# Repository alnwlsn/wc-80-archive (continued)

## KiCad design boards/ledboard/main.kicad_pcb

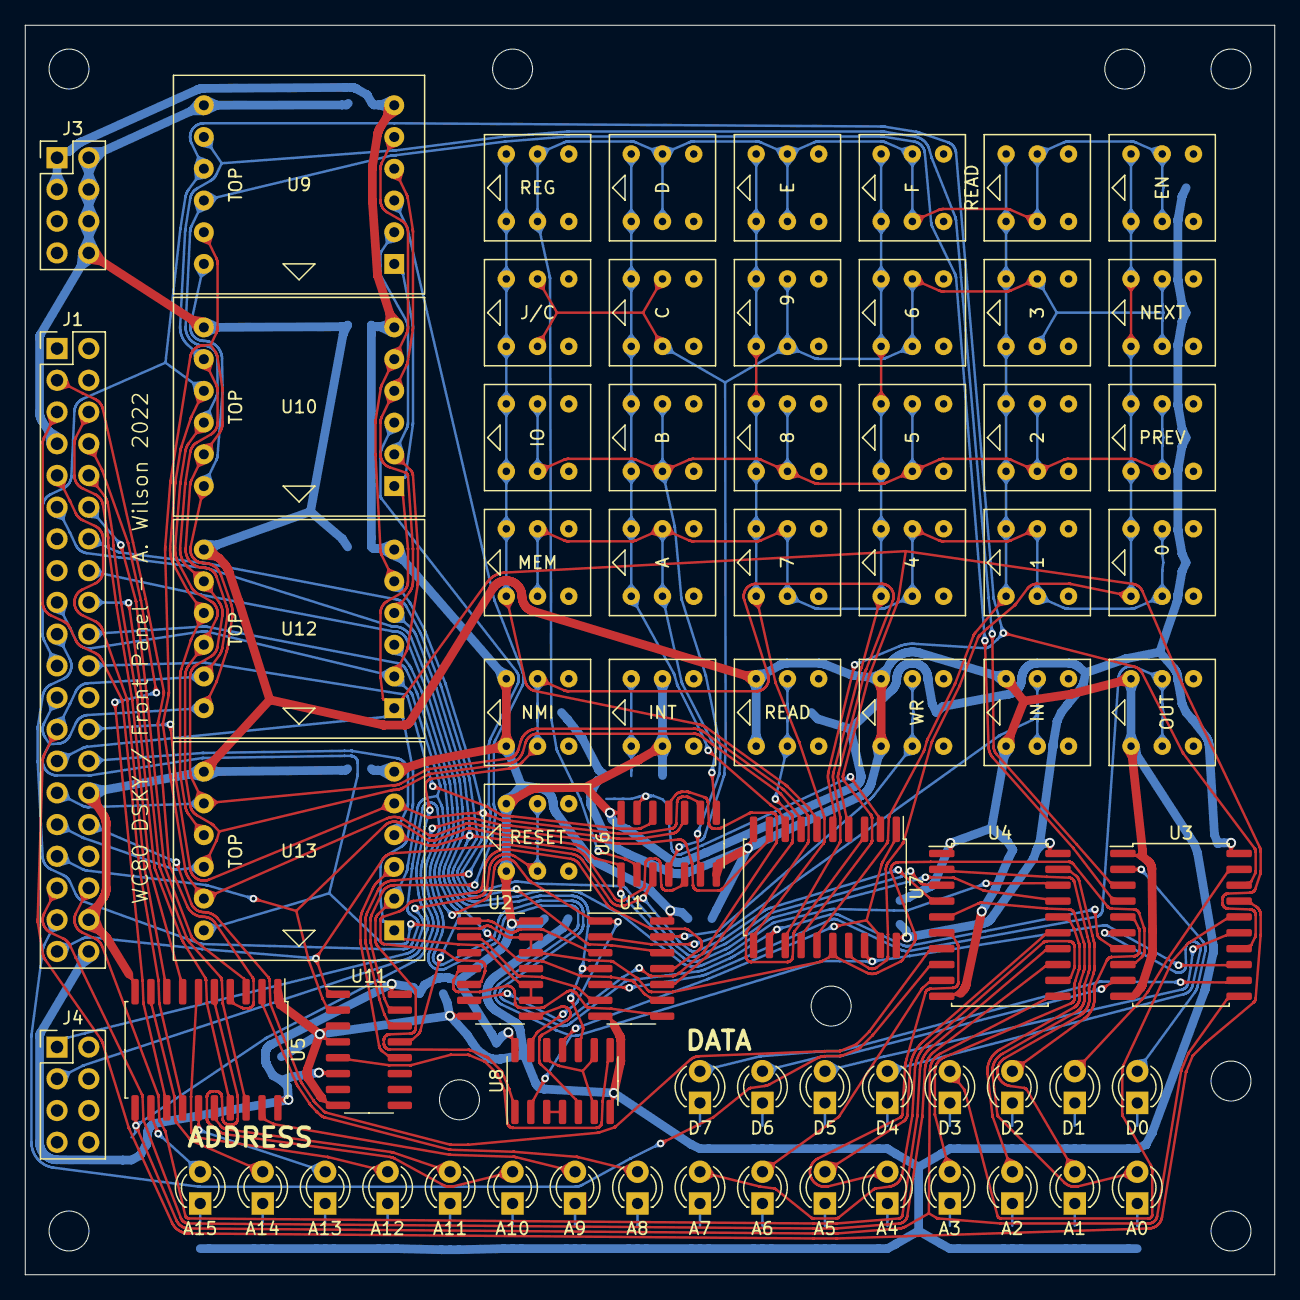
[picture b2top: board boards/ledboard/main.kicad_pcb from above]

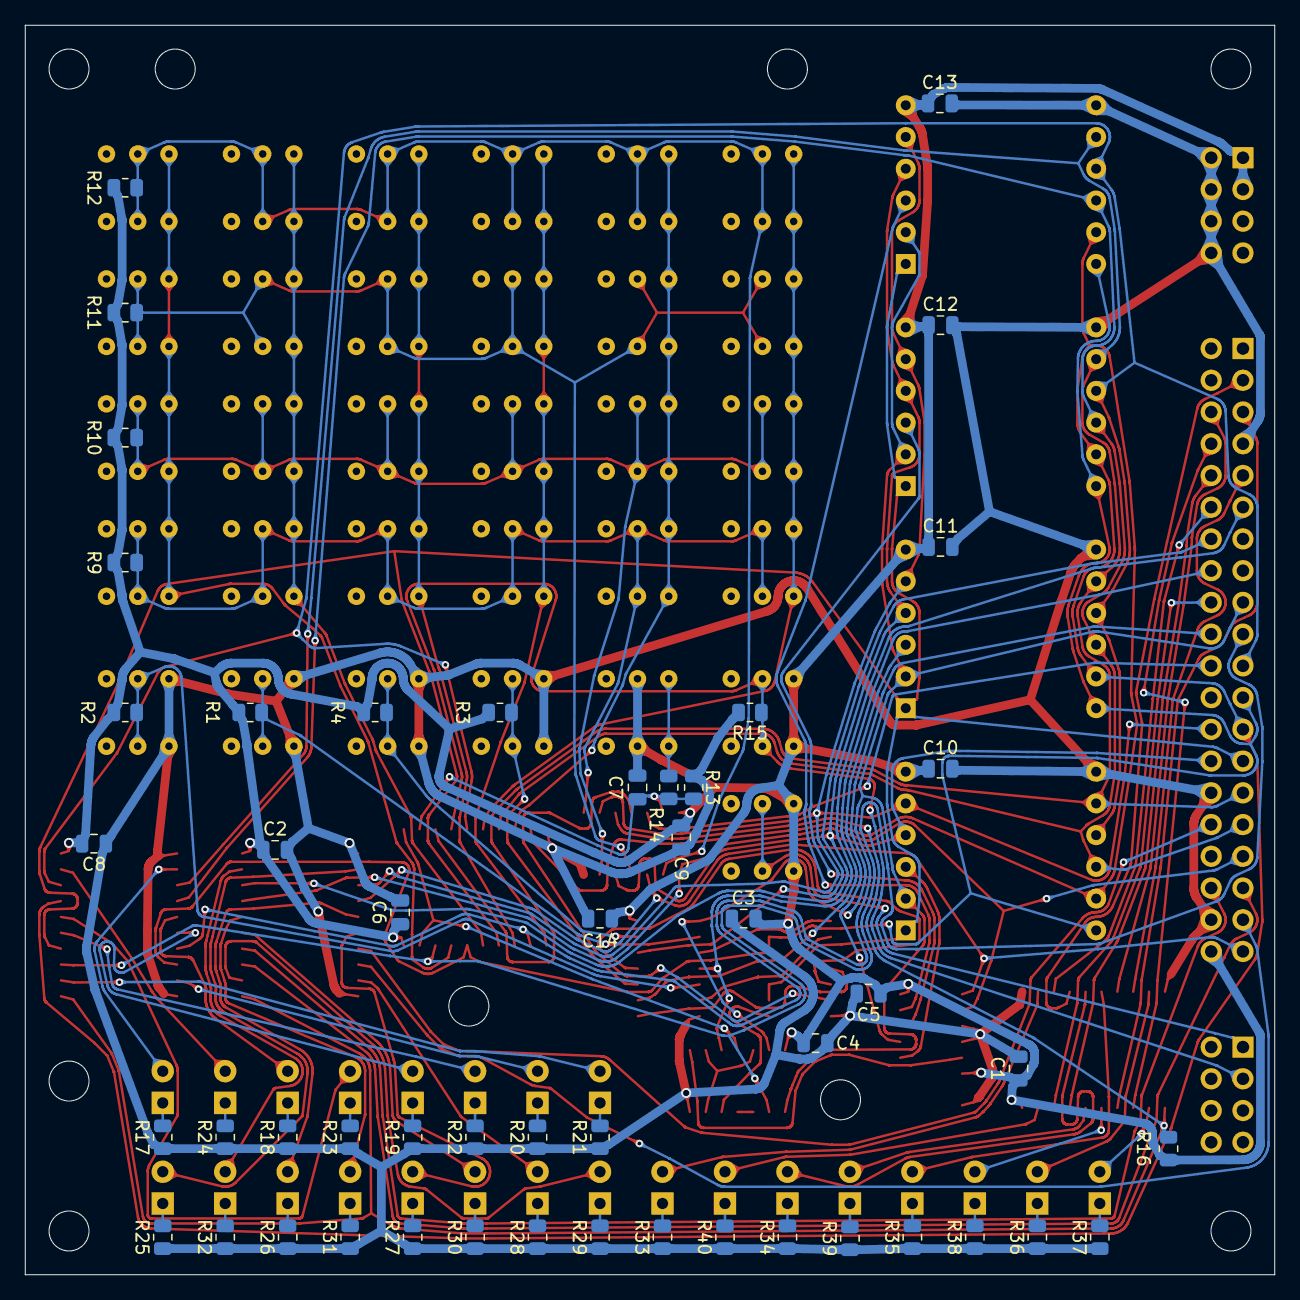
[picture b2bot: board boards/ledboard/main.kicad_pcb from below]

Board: 2 copper layers, 100.0 x 100.0 mm, 130 parts (50 on the bottom side), 112 nets.

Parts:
C1, C2, C3, C4, C5, C6, C7, C8, C9, C10, C11, C12, C13, C14: 100n; C_0805_2012Metric
D1: D0; LED_D3.0mm_FlatTop
D2: D2; LED_D3.0mm_FlatTop
D3: D4; LED_D3.0mm_FlatTop
D4: D6; LED_D3.0mm_FlatTop
D5: D7; LED_D3.0mm_FlatTop
D6: D5; LED_D3.0mm_FlatTop
D7: D3; LED_D3.0mm_FlatTop
D8: D1; LED_D3.0mm_FlatTop
D9: A0; LED_D3.0mm_FlatTop
D10: A2; LED_D3.0mm_FlatTop
D11: A4; LED_D3.0mm_FlatTop
D12: A6; LED_D3.0mm_FlatTop
D13: A7; LED_D3.0mm_FlatTop
D14: A5; LED_D3.0mm_FlatTop
D15: A3; LED_D3.0mm_FlatTop
D16: A1; LED_D3.0mm_FlatTop
D17: A8; LED_D3.0mm_FlatTop
D18: A10; LED_D3.0mm_FlatTop
D19: A12; LED_D3.0mm_FlatTop
D20: A14; LED_D3.0mm_FlatTop
D21: A15; LED_D3.0mm_FlatTop
D22: A13; LED_D3.0mm_FlatTop
D23: A11; LED_D3.0mm_FlatTop
D24: A9; LED_D3.0mm_FlatTop
H1, H2, H3, H4, H5, H6, H7, H8, H9: MountingHole; MountingHole_3.2mm_M3_DIN965
J1: TRS80W-header; PinHeader_2x20_P2.54mm_Vertical
J3, J4: Conn_02x04_Odd_Even; PinHeader_2x04_P2.54mm_Vertical
R1, R2, R3, R4, R9, R10, R11, R12, R13, R15, R16: 4.7K; R_0805_2012Metric
R14: 10; R_0805_2012Metric
R17, R18, R19, R20, R21, R22, R23, R24, R25, R26, R27, R28, R29, R30, R31, R32, R33, R34, R35, R36, R37, R38, R39, R40: 470; R_0805_2012Metric
SW1: IN; 8.5x8.5-DPDT-SP
SW2: OUT; 8.5x8.5-DPDT-SP
SW3, SW27: READ; 8.5x8.5-DPDT-SP
SW4: WR; 8.5x8.5-DPDT-SP
SW5: MEM; 8.5x8.5-DPDT-SP
SW6: A; 8.5x8.5-DPDT-SP
SW7: 7; 8.5x8.5-DPDT-SP
SW8: 4; 8.5x8.5-DPDT-SP
SW9: 1; 8.5x8.5-DPDT-SP
SW10: 0; 8.5x8.5-DPDT-SP
SW11: IO; 8.5x8.5-DPDT-SP
SW12: B; 8.5x8.5-DPDT-SP
SW13: 8; 8.5x8.5-DPDT-SP
SW14: 5; 8.5x8.5-DPDT-SP
SW15: 2; 8.5x8.5-DPDT-SP
SW16: PREV; 8.5x8.5-DPDT-SP
SW17: J/C; 8.5x8.5-DPDT-SP
SW18: C; 8.5x8.5-DPDT-SP
SW19: 9; 8.5x8.5-DPDT-SP
SW20: 6; 8.5x8.5-DPDT-SP
SW21: 3; 8.5x8.5-DPDT-SP
SW22: NEXT; 8.5x8.5-DPDT-SP
SW23: REG; 8.5x8.5-DPDT-SP
SW24: D; 8.5x8.5-DPDT-SP
SW25: E; 8.5x8.5-DPDT-SP
SW26: F; 8.5x8.5-DPDT-SP
SW28: EN; 8.5x8.5-DPDT-SP
SW29: INT; 8.5x8.5-DPDT-SP
SW30: RESET; 8.5x8.5-DPDT-SP
SW31: NMI; 8.5x8.5-DPDT-SP
U1, U8: 74LS32; SOIC-14_3.9x8.7mm_P1.27mm
U2: 74LS20; SOIC-14_3.9x8.7mm_P1.27mm
U3, U4, U5: 74LS374; SOIC-20W_7.5x12.8mm_P1.27mm
U6: 74LS06; SOIC-14_3.9x8.7mm_P1.27mm
U7: 74HCT244; SOIC-20W_7.5x12.8mm_P1.27mm
U9, U10, U12, U13: HPDL1414; DIP-24_W15.24mm_Socket
U11: 74LS138; SOIC-16_3.9x9.9mm_P1.27mm

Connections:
6x_IN: U7.1, U7.19, U8.11
6x_OUT: U8.8, U11.5
+5V: C1.1, C2.1, C3.1, C4.1, C5.1, C6.1, C7.2, C8.1, C9.1, C10.1, C11.1, C12.1, C13.1, C14.1, J1.40, J3.1, J3.3, R1.1, R2.1, R3.1, R4.1, R9.2, R10.2, R11.2, R12.2, R16.2, SW29.2, SW30.1, SW31.1, U1.14, U2.14, U3.20, U4.20, U5.20, U6.14, U7.20, U8.14, U9.6, U10.6, U11.6, U11.16, U12.6, U13.6
F_A0: J1.26, U4.3, U6.9, U9.5, U10.5, U12.5, U13.5
F_A1: J1.28, U4.18, U6.5, U9.4, U10.4, U12.4, U13.4
F_A2: J1.39, U4.4, U6.3, U11.1
F_A3: J1.33, U4.17, U6.1, U11.2
F_A4: J1.32, U4.7
F_A5: J1.36, U4.14
F_A6: J1.37, U4.8
F_A7: J1.35, U4.13
F_A8: J1.12, U5.3
F_A9: J1.18, U5.18
F_A10: J1.3, U5.4
F_A11: J1.10, U5.17
F_A12: J1.6, U5.7
F_A13: J1.5, U5.14
F_A14: J1.9, U5.8
F_A15: J1.8, U5.13
F_D0: J1.29, U3.3, U7.3, U9.8, U10.8, U12.8, U13.8
F_D1: J1.21, U3.18, U7.5, U9.9, U10.9, U12.9, U13.9
F_D2: J1.31, U3.4, U7.7, U9.10, U10.10, U12.10, U13.10
F_D3: J1.25, U3.17, U7.9, U9.11, U10.11, U12.11, U13.11
F_D4: J1.17, U3.7, U7.12, U8.1, U9.2, U10.2, U12.2, U13.2
F_D5: J1.27, U2.9, U2.10, U3.14, U7.14, U9.1, U10.1, U12.1, U13.1
F_D6: J1.23, U2.12, U2.13, U3.8, U7.16, U9.12, U10.12, U12.12, U13.12
F_D7: J1.19, U3.13, U7.18, U8.2
GND: C1.2, C2.2, C3.2, C4.2, C5.2, C6.2, C8.2, C9.2, C10.2, C11.2, C12.2, C13.2, C14.2, J1.7, J1.30, J1.38, J3.2, J3.4, J3.6, J3.8, R13.1, R15.2, R17.1, R18.1, R19.1, R20.1, R21.1, R22.1, R23.1, R24.1, R25.1, R26.1, R27.1, R28.1, R29.1, R30.1, R31.1, R32.1, R33.1, R34.1, R35.1, R36.1, R37.1, R38.1, R39.1, R40.1, SW1.1, SW2.1, SW3.1, SW4.1, U1.7, U2.7, U3.1, U3.10, U4.1, U4.10, U5.1, U5.10, U6.7, U7.10, U8.7, U9.7, U10.7, U11.3, U11.4, U11.8, U12.7, U13.7
unnamed: C7.1, R13.2, R14.2, U6.13, U7.2
unnamed: D1.1, R17.2
unnamed: D1.2, U3.2
unnamed: D2.1, R18.2
unnamed: D2.2, U3.5
unnamed: D3.1, R19.2
unnamed: D3.2, U3.6
unnamed: D4.1, R20.2
unnamed: D4.2, U3.9
unnamed: D5.1, R21.2
unnamed: D5.2, U3.12
unnamed: D6.1, R22.2
unnamed: D6.2, U3.15
unnamed: D7.1, R23.2
unnamed: D7.2, U3.16
unnamed: D8.1, R24.2
unnamed: D8.2, U3.19
unnamed: D9.1, R25.2
unnamed: D9.2, U4.2
unnamed: D10.1, R26.2
unnamed: D10.2, U4.5
unnamed: D11.1, R27.2
unnamed: D11.2, U4.6
unnamed: D12.1, R28.2
unnamed: D12.2, U4.9
unnamed: D13.1, R29.2
unnamed: D13.2, U4.12
unnamed: D14.1, R30.2
unnamed: D14.2, U4.15
unnamed: D15.1, R31.2
unnamed: D15.2, U4.16
unnamed: D16.1, R32.2
unnamed: D16.2, U4.19
unnamed: D17.1, R33.2
unnamed: D17.2, U5.2
unnamed: D18.1, R34.2
unnamed: D18.2, U5.5
unnamed: D19.1, R35.2
unnamed: D19.2, U5.6
unnamed: D20.1, R36.2
unnamed: D20.2, U5.9
unnamed: D21.1, R37.2
unnamed: D21.2, U5.12
unnamed: D22.1, R38.2
unnamed: D22.2, U5.15
unnamed: D23.1, R39.2
unnamed: D23.2, U5.16
unnamed: D24.1, R40.2
unnamed: D24.2, U5.19
unnamed: J4.1, SW30.2
unnamed: J4.3, R15.1, SW31.2, U7.4
unnamed: R1.2, SW1.2, U1.2
unnamed: R2.2, SW2.2, U1.5
unnamed: R3.2, SW3.2, U1.10
unnamed: R4.2, SW4.2, U1.13
unnamed: R9.1, SW5.2, SW6.2, SW7.2, SW8.2, SW9.2, SW10.2, U6.8
unnamed: R10.1, SW11.2, SW12.2, SW13.2, SW14.2, SW15.2, SW16.2, U6.6
unnamed: R11.1, SW17.2, SW18.2, SW19.2, SW20.2, SW21.2, SW22.2, U6.4
unnamed: R12.1, SW23.2, SW24.2, SW25.2, SW26.2, SW27.2, SW28.2, U6.2
unnamed: R14.1, SW29.1
unnamed: R16.1, U3.11, U4.11, U5.11, U6.10
unnamed: SW10.1, SW16.1, SW22.1, SW28.1, U7.17
unnamed: SW5.1, SW11.1, SW17.1, SW23.1, U7.6
unnamed: SW6.1, SW12.1, SW18.1, SW24.1, U7.8
unnamed: SW7.1, SW13.1, SW19.1, SW25.1, U7.11
unnamed: SW8.1, SW14.1, SW20.1, SW26.1, U7.13
unnamed: SW9.1, SW15.1, SW21.1, SW27.1, U7.15
unnamed: U1.3, U2.1
unnamed: U1.6, U2.2
unnamed: U1.8, U2.4
unnamed: U1.11, U2.5
unnamed: U2.6, U6.11
unnamed: U2.8, U8.5
unnamed: U8.3, U8.4
unnamed: U8.6, U8.9, U8.12
unnamed: U10.3, U11.14
unnamed: U11.12, U13.3
unnamed: U11.13, U12.3
unnamed: U9.3, U11.15
~F_INT~: J1.22, U6.12
~F_IN~: J1.20, U1.1, U8.13
~F_OUT~: J1.11, U1.4, U8.10
~F_READ~: J1.16, U1.9
~F_WRITE~: J1.14, U1.12

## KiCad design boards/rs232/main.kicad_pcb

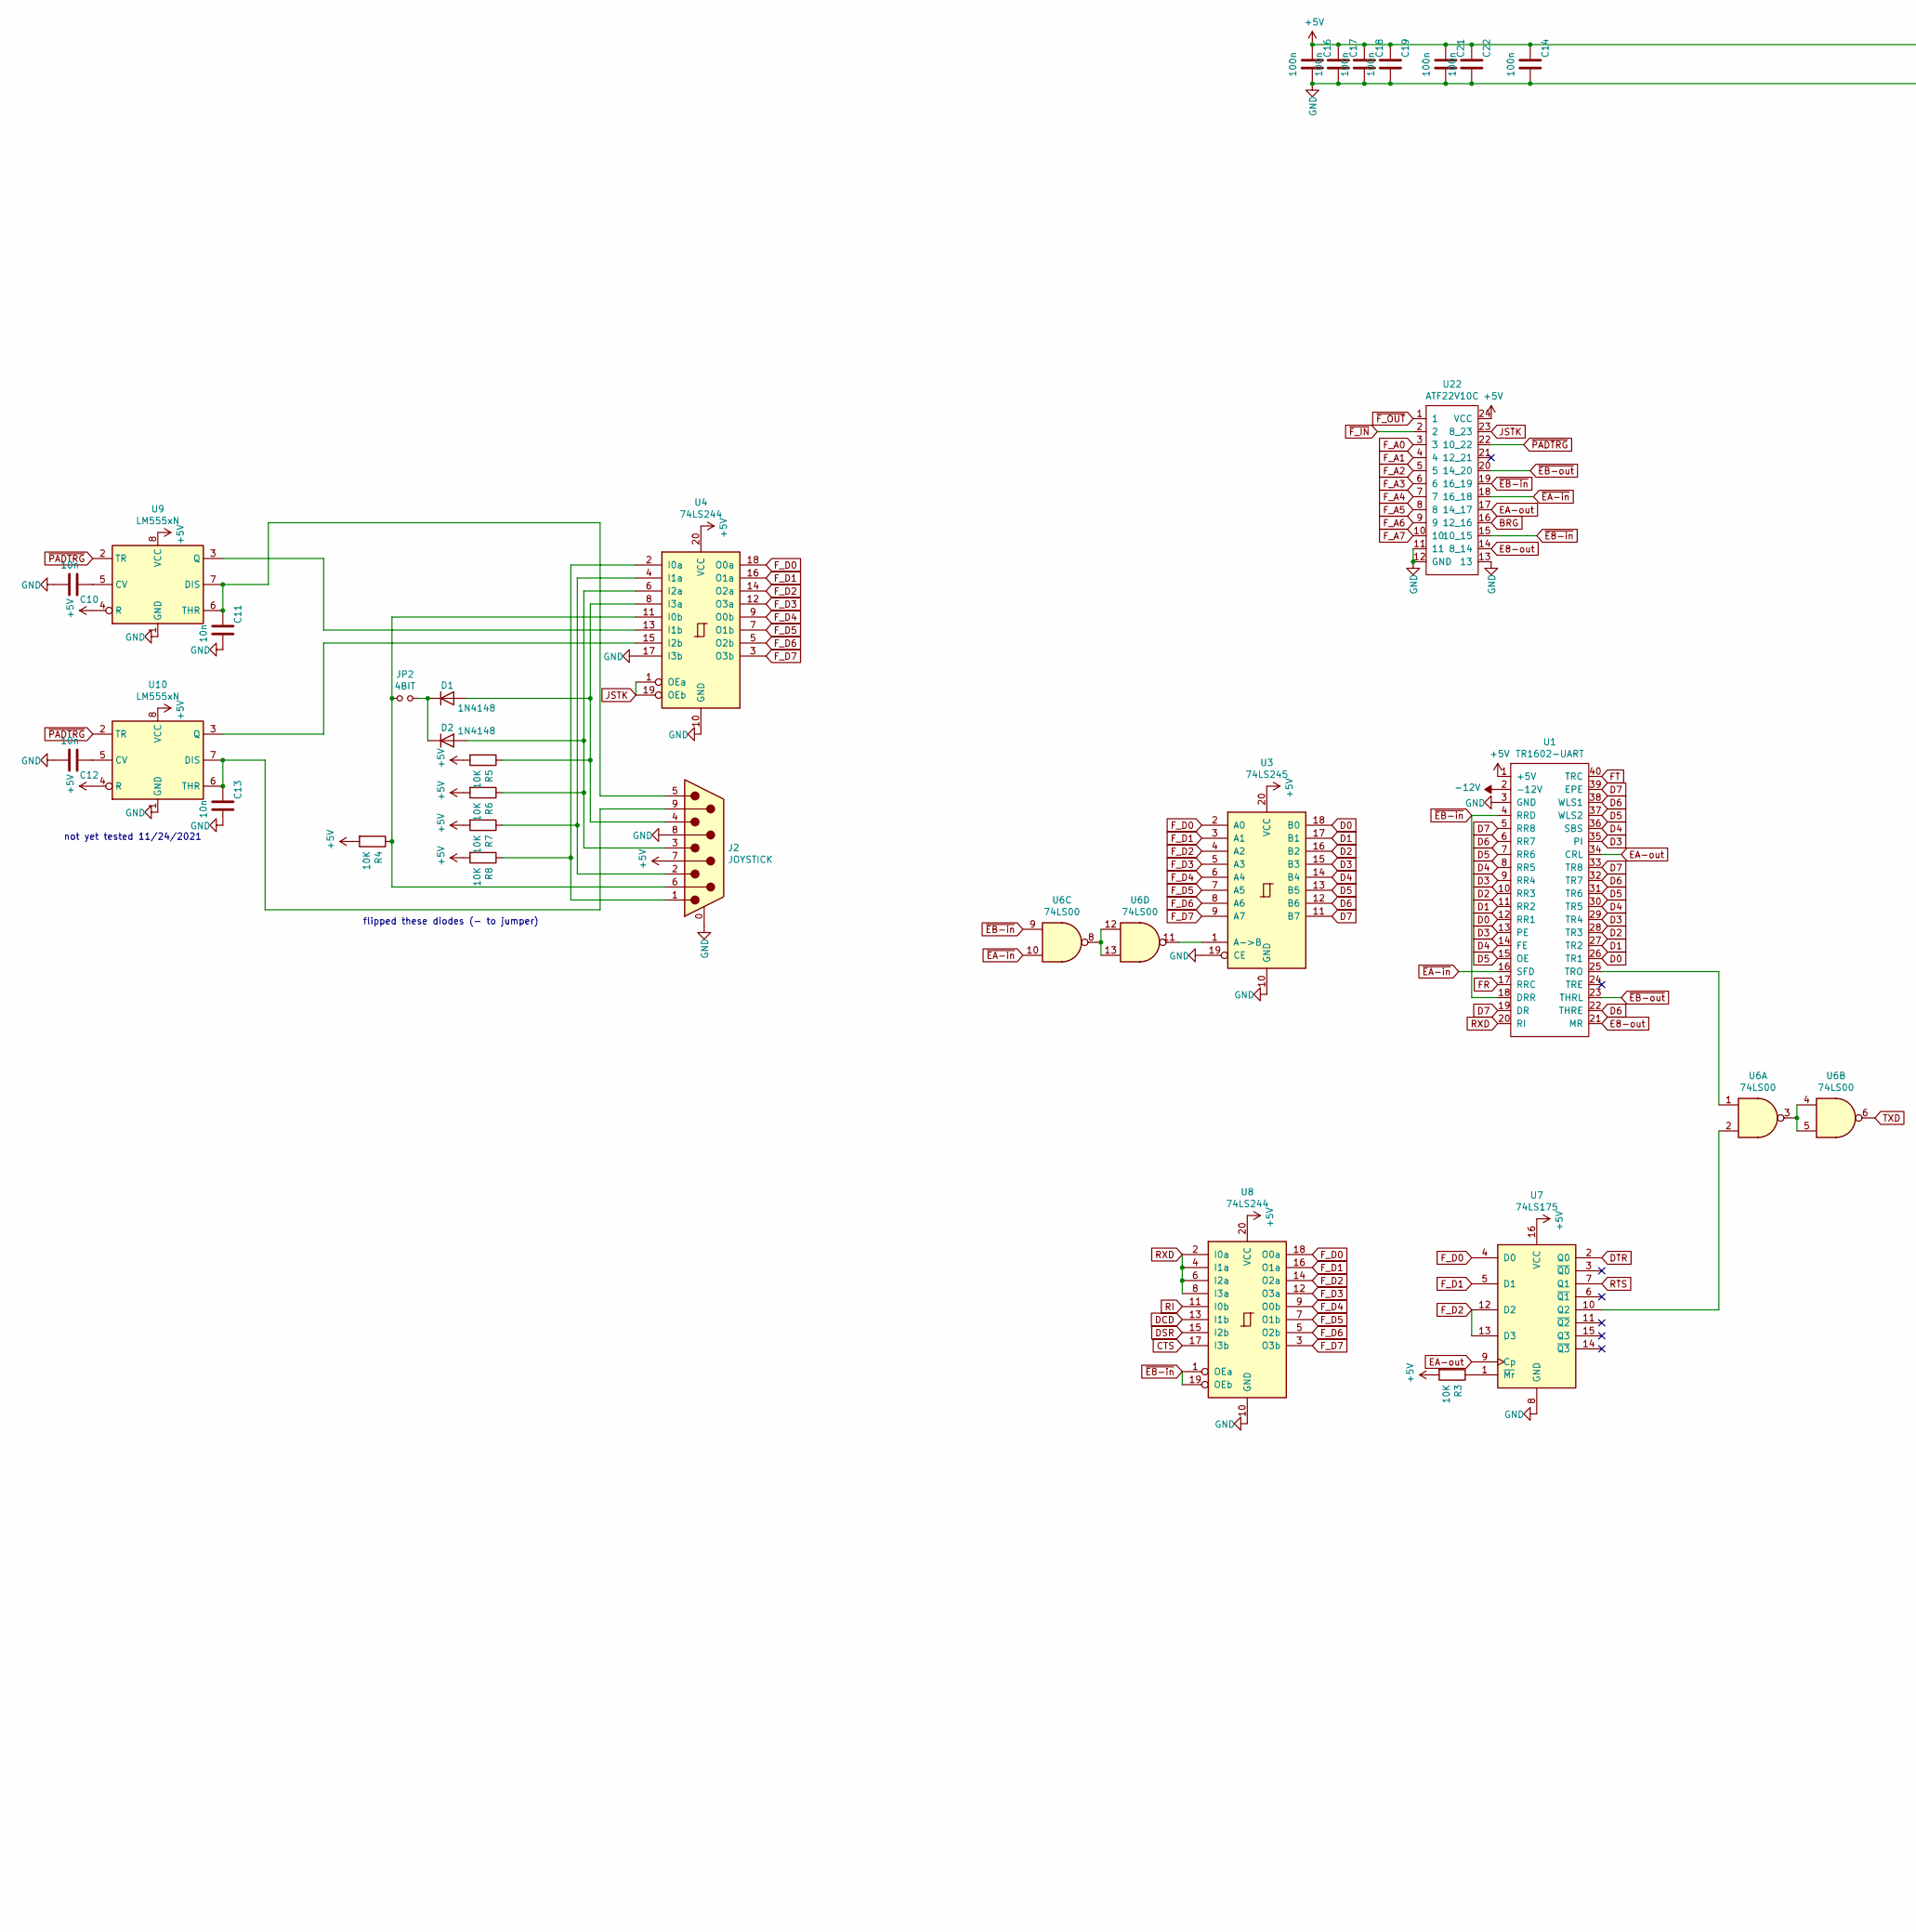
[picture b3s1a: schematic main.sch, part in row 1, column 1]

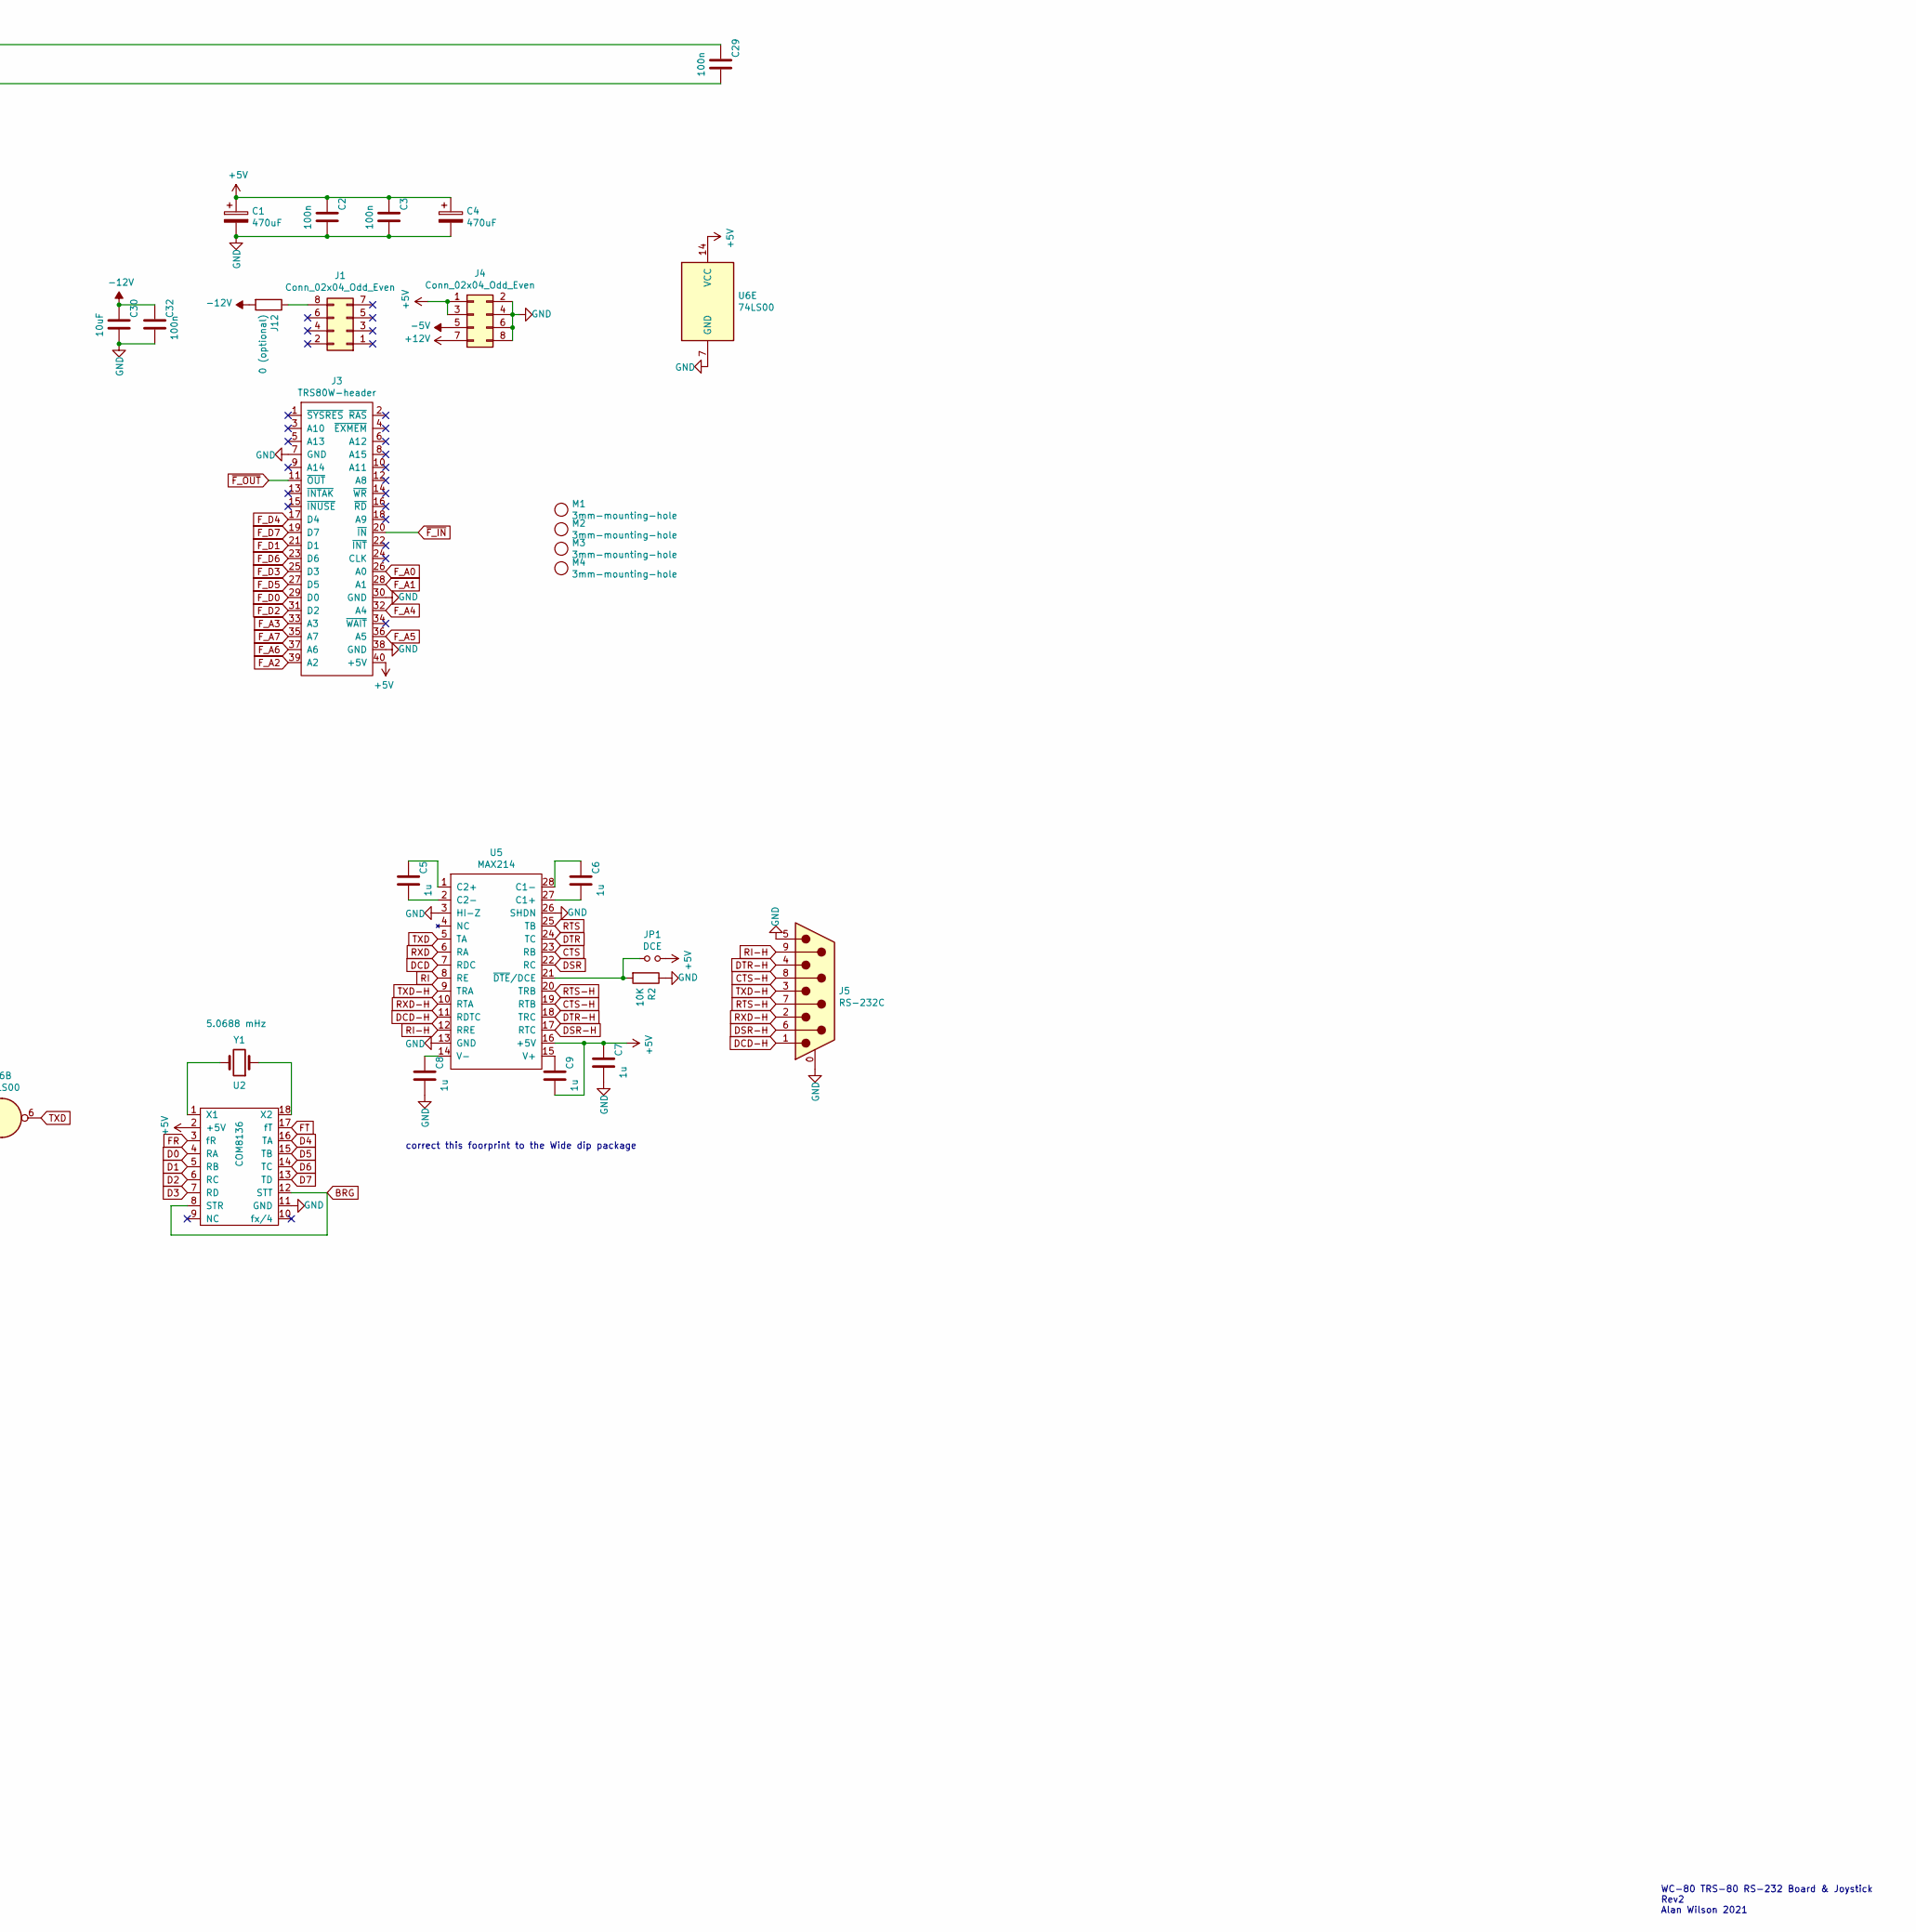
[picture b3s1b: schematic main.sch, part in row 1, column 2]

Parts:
C1, C4: 470uF; CP_Radial_D8.0mm_P3.50mm
C2, C3, C14, C16, C17, C18, C19, C21, C22, C29, C32: 100n; C_0805_2012Metric
C5, C6, C7, C8, C9: 1u; C_0805_2012Metric
C10, C11, C12, C13: 10n; C_0805_2012Metric
C30: 10uF; C_0805_2012Metric
D1, D2: 1N4148; D_DO-35_SOD27_P7.62mm_Horizontal
J1, J4: Conn_02x04_Odd_Even; PinHeader_2x04_P2.54mm_Vertical
J2: JOYSTICK; DS1037-09MNAKT74-0CC
J3: TRS80W-header; PinHeader_2x20_P2.54mm_Vertical
J5: RS-232C; DS1037-09MNAKT74-0CC
J12: 0 (optional); R_0805_2012Metric
JP1: DCE; PinHeader_1x02_P2.54mm_Vertical
JP2: 4BIT; PinHeader_1x02_P2.54mm_Vertical
M1, M2, M3, M4: 3mm-mounting-hole; MountingHole_3.2mm_M3_DIN965
R2, R3, R4, R5, R6, R7, R8: 10K; R_0805_2012Metric
U1: TR1602-UART; DIP-40_W15.24mm_Socket
U2: COM8136; DIP-18_W7.62mm_Socket
U3: 74LS245; DIP-20_W7.62mm_Socket
U4, U8: 74LS244; DIP-20_W7.62mm_Socket
U5: MAX214; DIP-28_W15.24mm_Socket
U6: 74LS00; DIP-14_W7.62mm_Socket
U7: 74LS175; DIP-16_W7.62mm_Socket
U9, U10: LM555xN; DIP-8_W7.62mm
U22: ATF22V10C; DIP-24_W7.62mm_Socket
Y1: 5.0688 mHz; Crystal_HC49-U_Horizontal

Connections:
+5V: C1.1, C2.1, C3.1, C4.1, C7.1, C9.2, C14.1, C16.1, C17.1, C18.1, C19.1, C21.1, C22.1, C29.1, J2.7, J3.40 (+5V), J4.1, J4.3, JP1.2, R3.2, R4.2, R5.2, R6.2, R7.2, R8.2, U1.1 (+5V), U2.2 (+5V), U3.20 (VCC), U4.20 (VCC), U5.16 (+5V), U6.14 (VCC), U7.16 (VCC), U8.20 (VCC), U9.4 (R), U9.8 (VCC), U10.4 (R), U10.8 (VCC), U22.24 (VCC)
+12V: J4.7
-5V: J4.5
-12V: C30.1, C32.1, J12.2, U1.2 (-12V)
BRG: U2.8 (STR), U2.12 (STT), U22.16 (12_16)
CTS: U5.23 (RB), U8.17 (I3b)
CTS-H: J5.8, U5.19 (RTB)
D0: U1.12 (RR1), U1.26 (TR1), U2.4 (RA), U3.18 (B0)
D1: U1.11 (RR2), U1.27 (TR2), U2.5 (RB), U3.17 (B1)
D2: U1.10 (RR3), U1.28 (TR3), U2.6 (RC), U3.16 (B2)
D3: U1.9 (RR4), U1.13 (PE), U1.29 (TR4), U1.35 (PI), U2.7 (RD), U3.15 (B3)
D4: U1.8 (RR5), U1.14 (FE), U1.30 (TR5), U1.36 (SBS), U2.16 (TA), U3.14 (B4)
D5: U1.7 (RR6), U1.15 (OE), U1.31 (TR6), U1.37 (WLS2), U2.15 (TB), U3.13 (B5)
D6: U1.6 (RR7), U1.22 (THRE), U1.32 (TR7), U1.38 (WLS1), U2.14 (TC), U3.12 (B6)
D7: U1.5 (RR8), U1.19 (DR), U1.33 (TR8), U1.39 (EPE), U2.13 (TD), U3.11 (B7)
DCD: U5.7 (RDC), U8.13 (I1b)
DCD-H: J5.1, U5.11 (RDTC)
DSR: U5.22 (RC), U8.15 (I2b)
DSR-H: J5.6, U5.17 (RTC)
DTR: U5.24 (TC), U7.2 (Q0)
DTR-H: J5.4, U5.18 (TRC)
E8-out: U1.21 (MR), U22.14 (8_14)
EA-out: U1.34 (CRL), U7.9 (Cp), U22.17 (14_17)
FR: U1.17 (RRC), U2.3 (fR)
FT: U1.40 (TRC), U2.17 (fT)
F_A0: J3.26 (A0), U22.3
F_A1: J3.28 (A1), U22.4
F_A2: J3.39 (A2), U22.5
F_A3: J3.33 (A3), U22.6
F_A4: J3.32 (A4), U22.7
F_A5: J3.36 (A5), U22.8
F_A6: J3.37 (A6), U22.9
F_A7: J3.35 (A7), U22.10
F_D0: J3.29 (D0), U3.2 (A0), U4.18 (O0a), U7.4 (D0), U8.18 (O0a)
F_D1: J3.21 (D1), U3.3 (A1), U4.16 (O1a), U7.5 (D1), U8.16 (O1a)
F_D2: J3.31 (D2), U3.4 (A2), U4.14 (O2a), U7.12 (D2), U7.13 (D3), U8.14 (O2a)
F_D3: J3.25 (D3), U3.5 (A3), U4.12 (O3a), U8.12 (O3a)
F_D4: J3.17 (D4), U3.6 (A4), U4.9 (O0b), U8.9 (O0b)
F_D5: J3.27 (D5), U3.7 (A5), U4.7 (O1b), U8.7 (O1b)
F_D6: J3.23 (D6), U3.8 (A6), U4.5 (O2b), U8.5 (O2b)
F_D7: J3.19 (D7), U3.9 (A7), U4.3 (O3b), U8.3 (O3b)
GND: C1.2, C2.2, C3.2, C4.2, C7.2, C8.2, C10.2, C11.2, C12.2, C13.2, C14.2, C16.2, C17.2, C18.2, C19.2, C21.2, C22.2, C29.2, C30.2, C32.2, J2.0 (PAD), J2.8, J3.7 (GND), J3.30 (GND), J3.38 (GND), J4.2, J4.4, J4.6, J4.8, J5.0 (PAD), J5.5, R2.1, U1.3 (GND), U2.11 (GND), U3.10 (GND), U3.19 (CE), U4.10 (GND), U4.17 (I3b), U5.3 (HI-Z), U5.13 (GND), U5.26 (SHDN), U6.7 (GND), U7.8 (GND), U8.10 (GND), U9.1 (GND), U10.1 (GND), U22.11, U22.12 (GND), U22.13
JSTK: U4.1 (OEa), U4.19 (OEb), U22.23 (8_23)
unnamed: C5.1, U5.1 (C2+)
unnamed: C5.2, U5.2 (C2-)
unnamed: C6.1, U5.28 (C1-)
unnamed: C6.2, U5.27 (C1+)
unnamed: C8.1, U5.14 (V-)
unnamed: C9.1, U5.15 (V+)
unnamed: C10.1, U9.5 (CV)
unnamed: C11.1, J2.5, U9.6 (THR), U9.7 (DIS)
unnamed: C12.1, U10.5 (CV)
unnamed: C13.1, J2.9, U10.6 (THR), U10.7 (DIS)
unnamed: J1.8, J12.1
unnamed: J2.1, R8.1, U4.2 (I0a)
unnamed: J2.2, R7.1, U4.4 (I1a)
unnamed: J2.6, JP2.1, R4.1, U4.11 (I0b)
unnamed: JP1.1, R2.2, U5.21 (~DTE~/DCE)
unnamed: R3.1, U7.1 (~Mr)
unnamed: U1.25 (TRO), U6.1
unnamed: U2.1 (X1), Y1.2
unnamed: U2.18 (X2), Y1.1
unnamed: U3.1 (A->B), U6.11
unnamed: U4.13 (I1b), U9.3 (Q)
unnamed: U6.2, U7.10 (Q2)
unnamed: U6.3, U6.4, U6.5
unnamed: U6.8, U6.12, U6.13
unnamed: U4.15 (I2b), U10.3 (Q)
RI: U5.8 (RE), U8.11 (I0b)
RI-H: J5.9, U5.12 (RRE)
RTS: U5.25 (TB), U7.7 (Q1)
RTS-H: J5.7, U5.20 (TRB)
RXD: U1.20 (RI), U5.6 (RA), U8.2 (I0a), U8.4 (I1a), U8.6 (I2a), U8.8 (I3a)
RXD-H: J5.2, U5.10 (RTA)
TXD: U5.5 (TA), U6.6
TXD-H: J5.3, U5.9 (TRA)
~E8-in~: U8.1 (OEa), U8.19 (OEb), U22.15 (10_15)
~EA-in~: U1.16 (SFD), U6.10, U22.18 (16_18)
~EB-in~: U1.4 (RRD), U1.18 (DRR), U6.9, U22.19 (16_19)
~EB-out~: U1.23 (THRL), U22.20 (14_20)
~F_IN~: J3.20 (~IN~), U22.2
~F_OUT~: J3.11 (~OUT~), U22.1
~PADTRG~: U9.2 (TR), U10.2 (TR), U22.22 (10_22)

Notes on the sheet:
WC-80 TRS-80 RS-232 Board & Joystick Rev2 Alan Wilson 2021
not yet tested 11/24/2021
flipped these diodes (- to jumper)
correct this foorprint to the Wide dip package

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
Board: 2 copper layers, 56 parts (29 on the bottom side), 84 nets, no tracks yet.
